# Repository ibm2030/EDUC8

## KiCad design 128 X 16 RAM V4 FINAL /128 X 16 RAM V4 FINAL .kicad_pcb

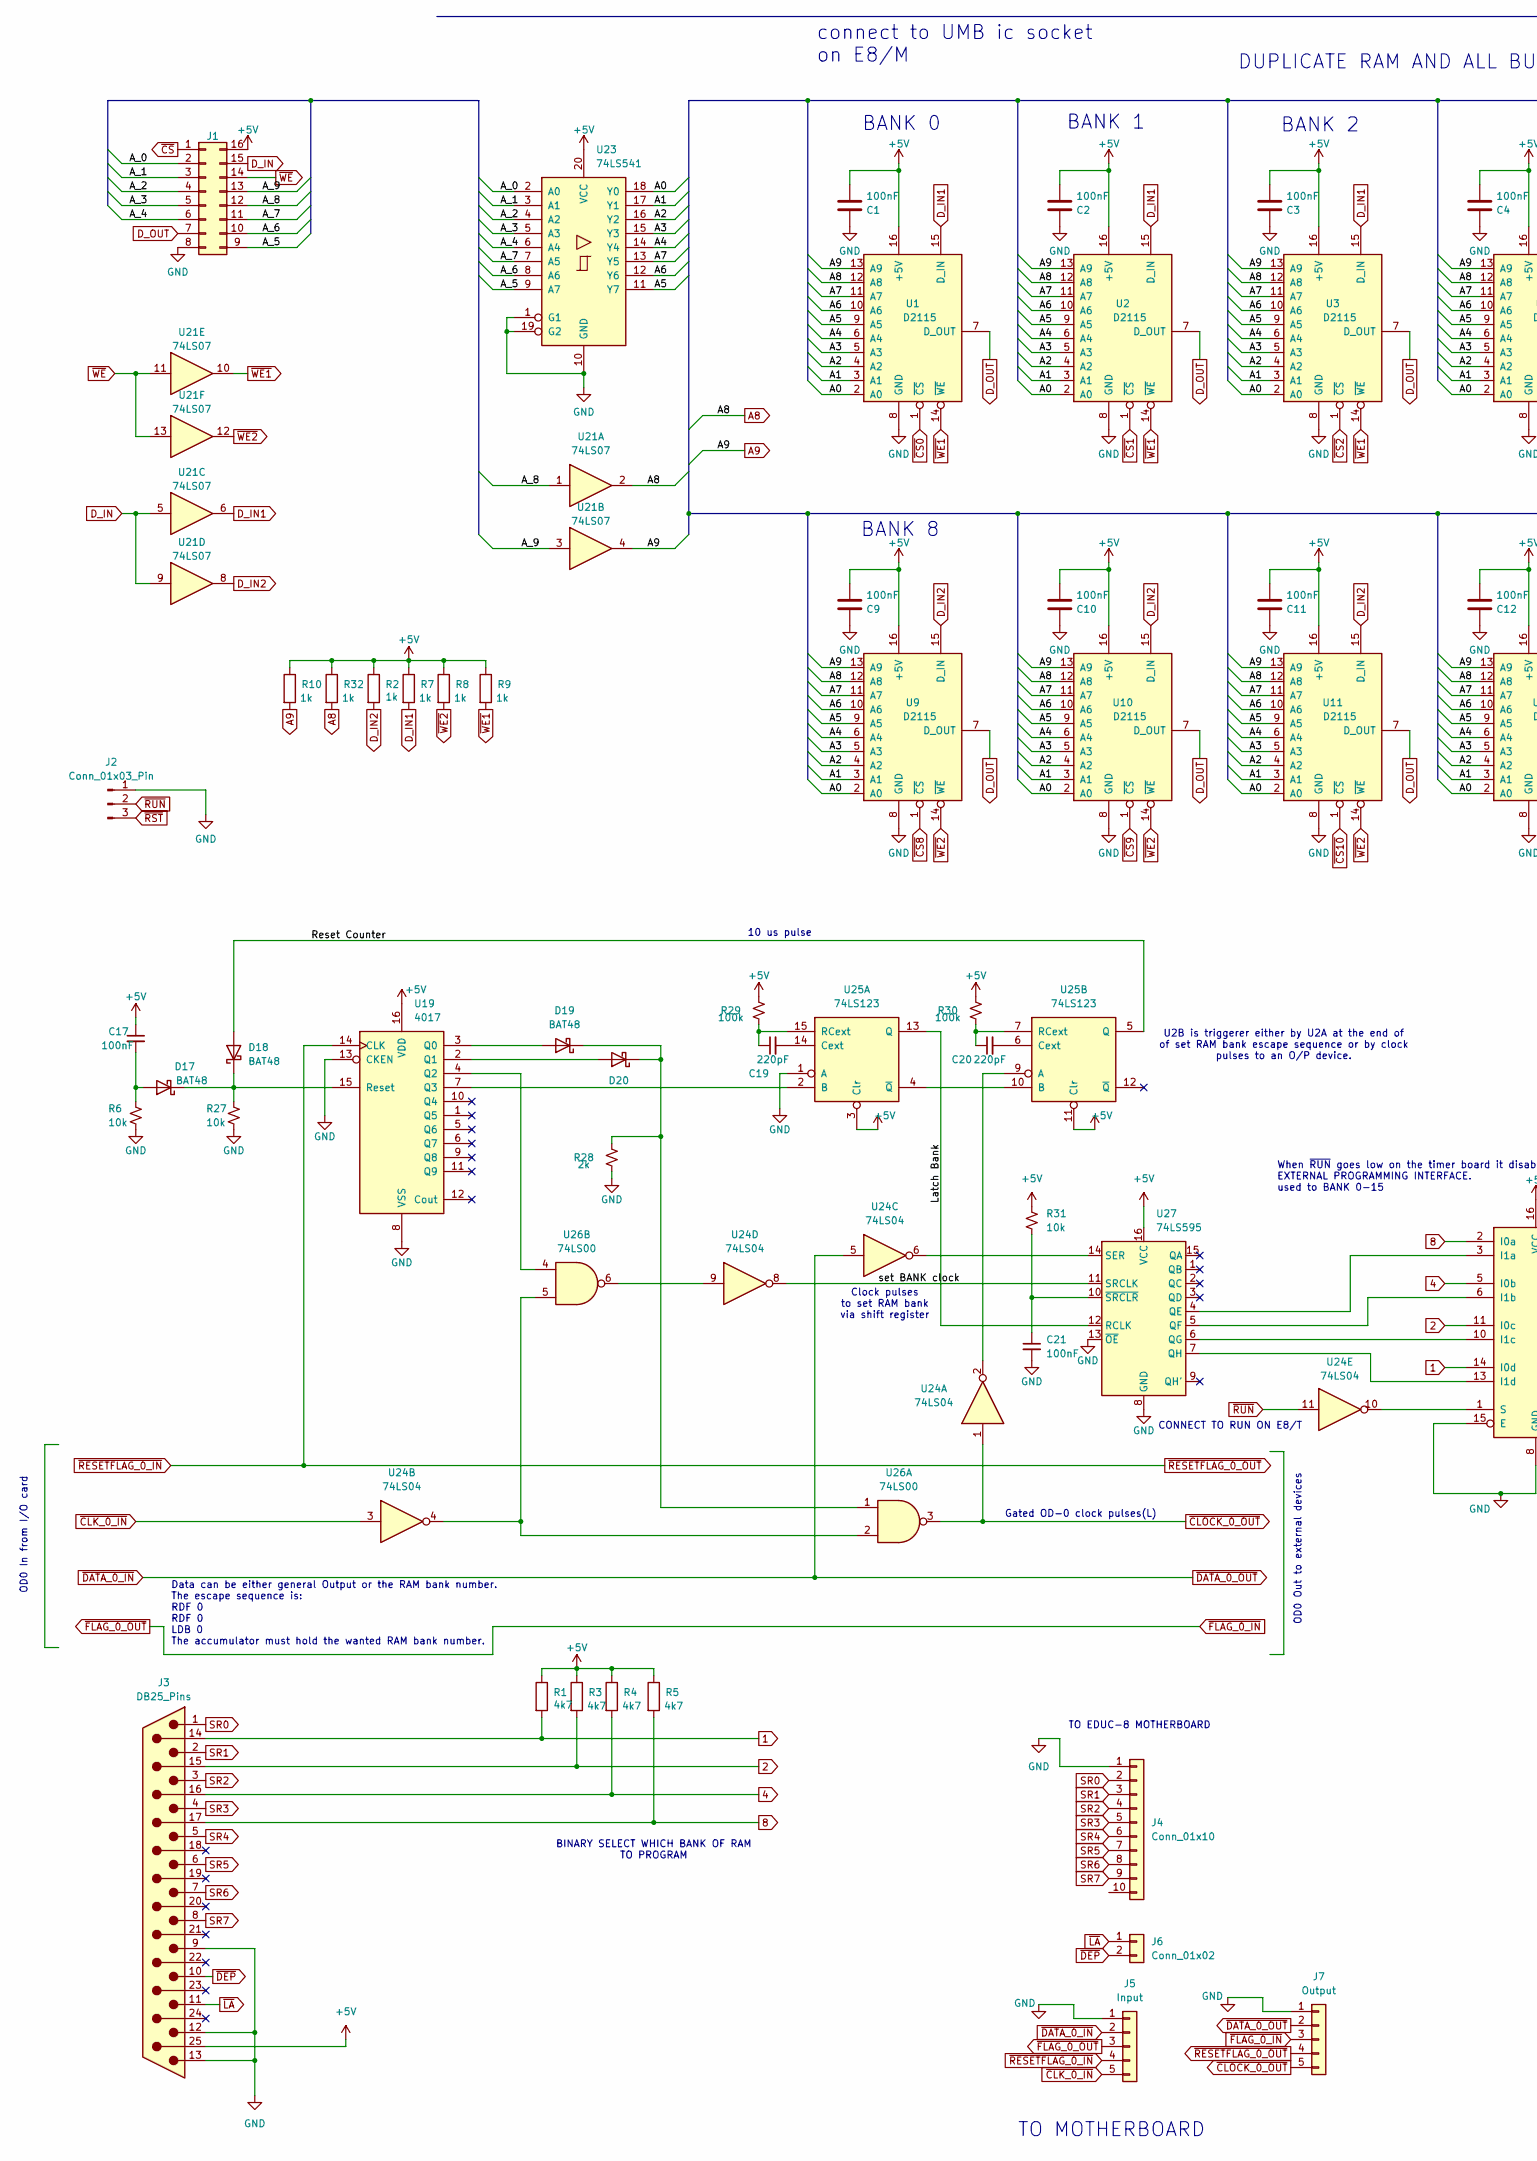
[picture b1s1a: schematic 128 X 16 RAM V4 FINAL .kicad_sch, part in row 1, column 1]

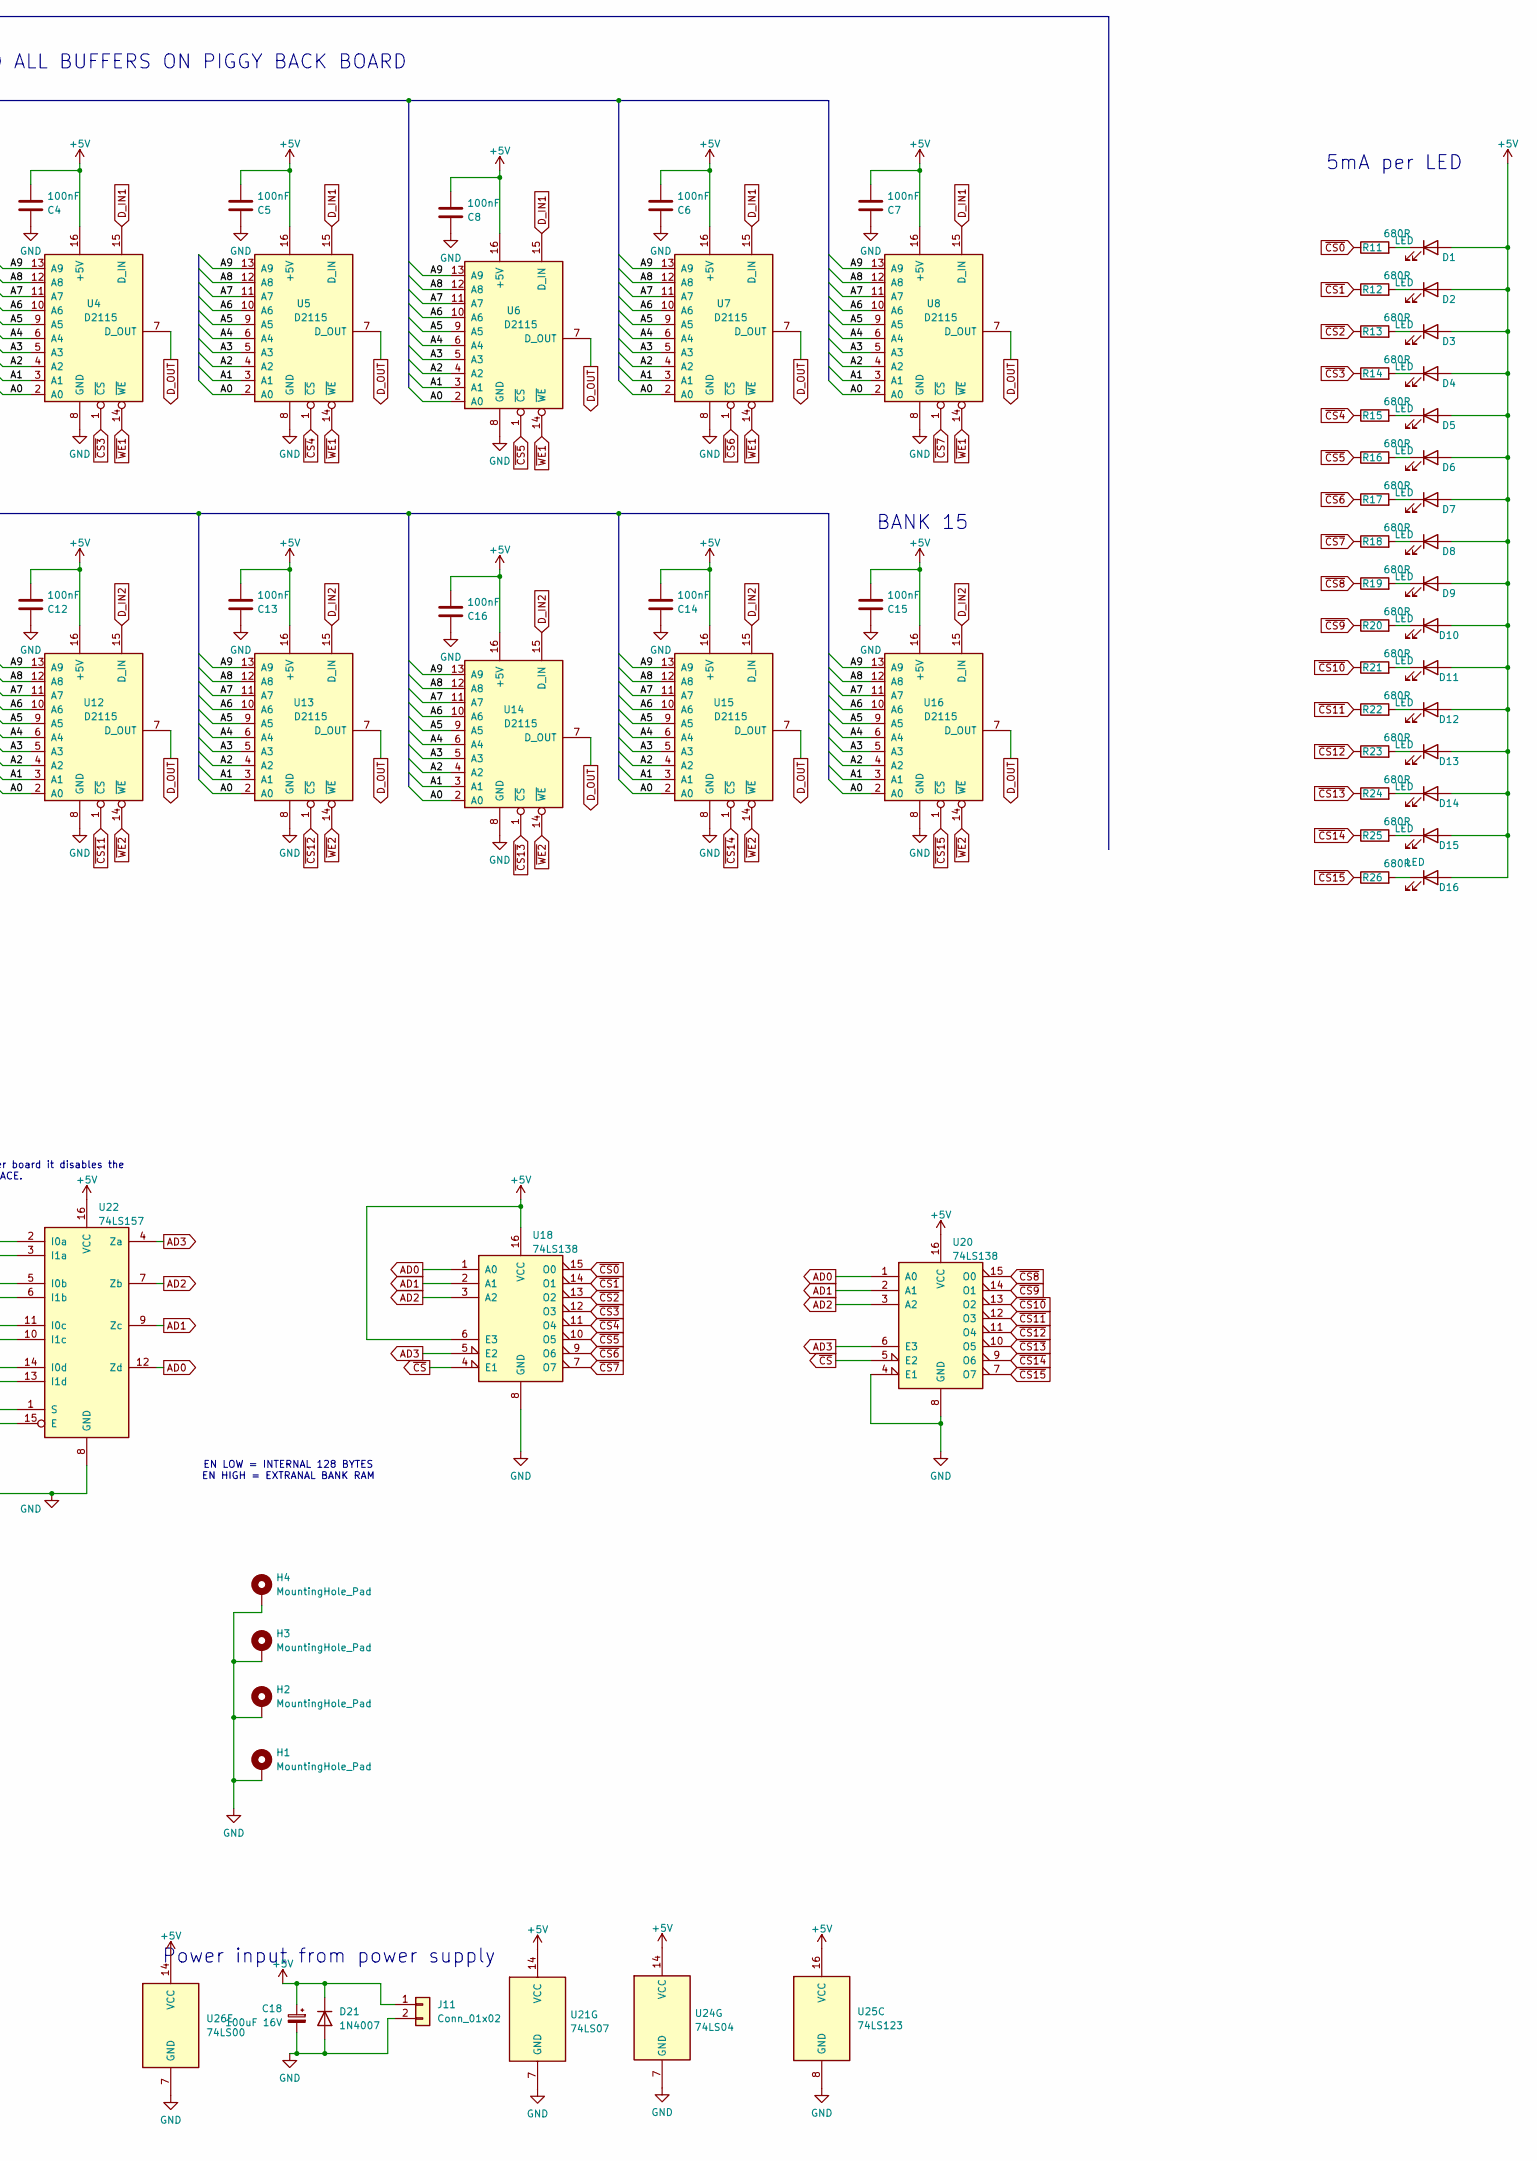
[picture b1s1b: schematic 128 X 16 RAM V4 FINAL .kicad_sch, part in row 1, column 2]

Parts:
C1, C2, C3, C4, C5, C6, C7, C8, C9, C10, C11, C12, C13, C14, C15, C16, C17, C21: 100nF; C_Disc_D4.3mm_W1.9mm_P5.00mm
C18: 100uF 16V; CP_Radial_D12.5mm_P5.00mm
C19, C20: 220pF; C_Disc_D4.3mm_W1.9mm_P5.00mm
D1, D2, D3, D4, D5, D6, D7, D8, D9, D10, D11, D12, D13, D14, D15, D16: LED; LED_D3.0mm
D17, D18, D19, D20: BAT48; D_DO-35_SOD27_P7.62mm_Horizontal
D21: 1N4007; D_DO-41_SOD81_P10.16mm_Horizontal
H1, H2, H3, H4: MountingHole_Pad; MountingHole_3.2mm_M3_DIN965_Pad
J1: Conn_02x08_Counter_Clockwise; DIP-16_W7.62mm_Socket_LongPads
J2: Conn_01x03_Pin; JST_XH_B3B-XH-A_1x03_P2.50mm_Vertical
J3: DB25_Pins; DSUB-25_Pins_Horizontal_P2.77x2.84mm_EdgePinOffset7.70mm_Ho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
J4: Conn_01x10; JST_XH_B10B-XH-A_1x10_P2.50mm_Vertical
J5: Input; JST_XH_B5B-XH-A_1x05_P2.50mm_Vertical
J6: Conn_01x02; JST_XH_B2B-XH-A_1x02_P2.50mm_Vertical
J7: Output; JST_XH_B5B-XH-A_1x05_P2.50mm_Vertical
J11: Conn_01x02; TerminalBlock_Phoenix_MKDS-1,5-2-5.08_1x02_P5.08mm_Horizont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
R1, R3, R4, R5: 4k7; R_Axial_DIN0207_L6.3mm_D2.5mm_P10.16mm_Horizontal
R2, R7, R8, R9, R10, R32: 1k; R_Axial_DIN0207_L6.3mm_D2.5mm_P10.16mm_Horizontal
R6, R27, R31: 10k; R_Axial_DIN0207_L6.3mm_D2.5mm_P10.16mm_Horizontal
R11, R12, R13, R14, R15, R16, R17, R18, R19, R20, R21, R22, R23, R24, R25, R26: 680R; R_Axial_DIN0207_L6.3mm_D2.5mm_P10.16mm_Horizontal
R28: 2k; R_Axial_DIN0207_L6.3mm_D2.5mm_P10.16mm_Horizontal
R29, R30: 100k; R_Axial_DIN0207_L6.3mm_D2.5mm_P10.16mm_Horizontal
U1, U2, U3, U4, U5, U6, U7, U8, U9, U10, U11, U12, U13, U14, U15, U16: D2115; DIP-16_W7.62mm_LongPads
U18, U20: 74LS138; DIP-16_W7.62mm_LongPads
U19: 4017; DIP-16_W7.62mm_LongPads
U21: 74LS07; DIP-14_W7.62mm_LongPads
U22: 74LS157; DIP-16_W7.62mm_LongPads
U23: 74LS541; DIP-20_W7.62mm_LongPads
U24: 74LS04; DIP-14_W7.62mm_LongPads
U25: 74LS123; DIP-16_W7.62mm_LongPads
U26: 74LS00; DIP-14_W7.62mm_LongPads
U27: 74LS595

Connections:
1: J3.14, R1.2, U22.14 (I0d)
2: J3.15, R3.2, U22.11 (I0c)
4: J3.16, R4.2, U22.5 (I0b)
8: J3.17, R5.2, U22.2 (I0a)
+5V: C1.2, C2.2, C3.2, C4.2, C5.2, C6.2, C7.2, C8.2, C9.2, C10.2, C11.2, C12.2, C13.2, C14.2, C15.2, C16.2, C17.1, C18.1, D1.2 (A), D2.2 (A), D3.2 (A), D4.2 (A), D5.2 (A), D6.2 (A), D7.2 (A), D8.2 (A), D9.2 (A), D10.2 (A), D11.2 (A), D12.2 (A), D13.2 (A), D14.2 (A), D15.2 (A), D16.2 (A), D21.1 (K), J1.16, J3.25, J11.1, R1.1, R2.1, R3.1, R4.1, R5.1, R7.1, R8.1, R9.1, R10.1, R29.1, R30.1, R31.1, R32.1, U1.16 (+5V), U2.16 (+5V), U3.16 (+5V), U4.16 (+5V), U5.16 (+5V), U6.16 (+5V), U7.16 (+5V), U8.16 (+5V), U9.16 (+5V), U10.16 (+5V), U11.16 (+5V), U12.16 (+5V), U13.16 (+5V), U14.16 (+5V), U15.16 (+5V), U16.16 (+5V), U18.6 (E3), U18.16 (VCC), U19.16 (VDD), U20.16 (VCC), U21.14 (VCC), U22.16 (VCC), U23.20 (VCC), U24.14 (VCC), U25.3 (Clr), U25.11 (Clr), U25.16 (VCC), U26.14 (VCC), U27.16 (VCC)
/A0: U1.2 (A0), U2.2 (A0), U3.2 (A0), U4.2 (A0), U5.2 (A0), U6.2 (A0), U7.2 (A0), U8.2 (A0), U9.2 (A0), U10.2 (A0), U11.2 (A0), U12.2 (A0), U13.2 (A0), U14.2 (A0), U15.2 (A0), U16.2 (A0), U23.18 (Y0)
/A1: U1.3 (A1), U2.3 (A1), U3.3 (A1), U4.3 (A1), U5.3 (A1), U6.3 (A1), U7.3 (A1), U8.3 (A1), U9.3 (A1), U10.3 (A1), U11.3 (A1), U12.3 (A1), U13.3 (A1), U14.3 (A1), U15.3 (A1), U16.3 (A1), U23.17 (Y1)
/A2: U1.4 (A2), U2.4 (A2), U3.4 (A2), U4.4 (A2), U5.4 (A2), U6.4 (A2), U7.4 (A2), U8.4 (A2), U9.4 (A2), U10.4 (A2), U11.4 (A2), U12.4 (A2), U13.4 (A2), U14.4 (A2), U15.4 (A2), U16.4 (A2), U23.16 (Y2)
/A3: U1.5 (A3), U2.5 (A3), U3.5 (A3), U4.5 (A3), U5.5 (A3), U6.5 (A3), U7.5 (A3), U8.5 (A3), U9.5 (A3), U10.5 (A3), U11.5 (A3), U12.5 (A3), U13.5 (A3), U14.5 (A3), U15.5 (A3), U16.5 (A3), U23.15 (Y3)
/A4: U1.6 (A4), U2.6 (A4), U3.6 (A4), U4.6 (A4), U5.6 (A4), U6.6 (A4), U7.6 (A4), U8.6 (A4), U9.6 (A4), U10.6 (A4), U11.6 (A4), U12.6 (A4), U13.6 (A4), U14.6 (A4), U15.6 (A4), U16.6 (A4), U23.14 (Y4)
/A5: U1.9 (A5), U2.9 (A5), U3.9 (A5), U4.9 (A5), U5.9 (A5), U6.9 (A5), U7.9 (A5), U8.9 (A5), U9.9 (A5), U10.9 (A5), U11.9 (A5), U12.9 (A5), U13.9 (A5), U14.9 (A5), U15.9 (A5), U16.9 (A5), U23.11 (Y7)
/A6: U1.10 (A6), U2.10 (A6), U3.10 (A6), U4.10 (A6), U5.10 (A6), U6.10 (A6), U7.10 (A6), U8.10 (A6), U9.10 (A6), U10.10 (A6), U11.10 (A6), U12.10 (A6), U13.10 (A6), U14.10 (A6), U15.10 (A6), U16.10 (A6), U23.12 (Y6)
/A7: U1.11 (A7), U2.11 (A7), U3.11 (A7), U4.11 (A7), U5.11 (A7), U6.11 (A7), U7.11 (A7), U8.11 (A7), U9.11 (A7), U10.11 (A7), U11.11 (A7), U12.11 (A7), U13.11 (A7), U14.11 (A7), U15.11 (A7), U16.11 (A7), U23.13 (Y5)
/A_0: J1.2, U23.2 (A0)
/A_1: J1.3, U23.3 (A1)
/A_2: J1.4, U23.4 (A2)
/A_3: J1.5, U23.5 (A3)
/A_4: J1.6, U23.6 (A4)
/A_5: J1.9, U23.9 (A7)
/A_6: J1.10, U23.8 (A6)
/A_7: J1.11, U23.7 (A5)
/A_8: J1.12, U21.1
/A_9: J1.13, U21.3
/Latch Bank: U25.13 (Q), U27.12 (RCLK)
/Reset Counter: D18.2 (A), U25.5 (Q)
/set BANK clock: U24.8, U27.11 (SRCLK)
A8: R32.2, U1.12 (A8), U2.12 (A8), U3.12 (A8), U4.12 (A8), U5.12 (A8), U6.12 (A8), U7.12 (A8), U8.12 (A8), U9.12 (A8), U10.12 (A8), U11.12 (A8), U12.12 (A8), U13.12 (A8), U14.12 (A8), U15.12 (A8), U16.12 (A8), U21.2
A9: R10.2, U1.13 (A9), U2.13 (A9), U3.13 (A9), U4.13 (A9), U5.13 (A9), U6.13 (A9), U7.13 (A9), U8.13 (A9), U9.13 (A9), U10.13 (A9), U11.13 (A9), U12.13 (A9), U13.13 (A9), U14.13 (A9), U15.13 (A9), U16.13 (A9), U21.4
AD0: U18.1 (A0), U20.1 (A0), U22.12 (Zd)
AD1: U18.2 (A1), U20.2 (A1), U22.9 (Zc)
AD2: U18.3 (A2), U20.3 (A2), U22.7 (Zb)
AD3: U18.5 (E2), U20.6 (E3), U22.4 (Za)
D_IN: J1.15, U21.5, U21.9
D_IN1: R7.2, U1.15 (D_IN), U2.15 (D_IN), U3.15 (D_IN), U4.15 (D_IN), U5.15 (D_IN), U6.15 (D_IN), U7.15 (D_IN), U8.15 (D_IN), U21.6
D_IN2: R2.2, U9.15 (D_IN), U10.15 (D_IN), U11.15 (D_IN), U12.15 (D_IN), U13.15 (D_IN), U14.15 (D_IN), U15.15 (D_IN), U16.15 (D_IN), U21.8
D_OUT: J1.7, U1.7 (D_OUT), U2.7 (D_OUT), U3.7 (D_OUT), U4.7 (D_OUT), U5.7 (D_OUT), U6.7 (D_OUT), U7.7 (D_OUT), U8.7 (D_OUT), U9.7 (D_OUT), U10.7 (D_OUT), U11.7 (D_OUT), U12.7 (D_OUT), U13.7 (D_OUT), U14.7 (D_OUT), U15.7 (D_OUT), U16.7 (D_OUT)
GND: C1.1, C2.1, C3.1, C4.1, C5.1, C6.1, C7.1, C8.1, C9.1, C10.1, C11.1, C12.1, C13.1, C14.1, C15.1, C16.1, C18.2, C21.2, D21.2 (A), H1.1, H2.1, H3.1, H4.1, J1.8, J2.1, J3.9, J3.12, J3.13, J4.1, J5.1, J7.1, J11.2, R6.2, R27.2, R28.2, U1.8 (GND), U2.8 (GND), U3.8 (GND), U4.8 (GND), U5.8 (GND), U6.8 (GND), U7.8 (GND), U8.8 (GND), U9.8 (GND), U10.8 (GND), U11.8 (GND), U12.8 (GND), U13.8 (GND), U14.8 (GND), U15.8 (GND), U16.8 (GND), U18.8 (GND), U19.8 (VSS), U19.13 (CKEN), U20.4 (E1), U20.8 (GND), U21.7 (GND), U22.8 (GND), U22.15 (E), U23.1 (G1), U23.10 (GND), U23.19 (G2), U24.7 (GND), U25.1 (A), U25.8 (GND), U26.7 (GND), U27.8 (GND), U27.13 (~OE)
unnamed: D1.1 (K), R11.2
unnamed: D2.1 (K), R12.2
unnamed: D3.1 (K), R13.2
unnamed: D4.1 (K), R14.2
unnamed: D5.1 (K), R15.2
unnamed: D6.1 (K), R16.2
unnamed: D7.1 (K), R17.2
unnamed: D8.1 (K), R18.2
unnamed: D9.1 (K), R19.2
unnamed: D10.1 (K), R20.2
unnamed: D11.1 (K), R21.2
unnamed: D12.1 (K), R22.2
unnamed: D13.1 (K), R23.2
unnamed: D14.1 (K), R24.2
unnamed: D15.1 (K), R25.2
unnamed: D16.1 (K), R26.2
unnamed: C17.2, D17.2 (A), R6.1
unnamed: D17.1 (K), D18.1 (K), R27.1, U19.15 (Reset)
unnamed: D19.2 (A), U19.3 (Q0)
unnamed: D19.1 (K), D20.1 (K), R28.1, U26.1
unnamed: D20.2 (A), U19.2 (Q1)
unnamed: U19.4 (Q2), U26.4
unnamed: U19.7 (Q3), U25.2 (B)
unnamed: U22.3 (I1a), U27.4 (QE)
unnamed: U22.6 (I1b), U27.5 (QF)
unnamed: U22.10 (I1c), U27.6 (QG)
unnamed: U22.13 (I1d), U27.7 (QH)
unnamed: U22.1 (S), U24.10
unnamed: U24.4, U26.2, U26.5
unnamed: U24.9, U26.6
unnamed: C19.2, U25.14 (Cext)
unnamed: C19.1, R29.2, U25.15 (RCext)
unnamed: U25.4 (~Q), U25.10 (B)
unnamed: U24.2, U25.9 (A)
unnamed: C20.2, U25.6 (Cext)
unnamed: C20.1, R30.2, U25.7 (RCext)
unnamed: U24.6, U27.14 (SER)
unnamed: C21.1, R31.2, U27.10 (~SRCLR)
SR0: J3.1, J4.2
SR1: J3.2, J4.3
SR2: J3.3, J4.4
SR3: J3.4, J4.5
SR4: J3.5, J4.6
SR5: J3.6, J4.7
SR6: J3.7, J4.8
SR7: J3.8, J4.9
~CLK_0_IN: J5.5, U24.3
~CLOCK_0_OUT: J7.5, U24.1, U26.3
~CS0: R11.1, U1.1 (~CS), U18.15 (O0)
~CS1: R12.1, U2.1 (~CS), U18.14 (O1)
~CS2: R13.1, U3.1 (~CS), U18.13 (O2)
~CS3: R14.1, U4.1 (~CS), U18.12 (O3)
~CS4: R15.1, U5.1 (~CS), U18.11 (O4)
~CS5: R16.1, U6.1 (~CS), U18.10 (O5)
~CS6: R17.1, U7.1 (~CS), U18.9 (O6)
~CS7: R18.1, U8.1 (~CS), U18.7 (O7)
~CS8: R19.1, U9.1 (~CS), U20.15 (O0)
~CS9: R20.1, U10.1 (~CS), U20.14 (O1)
~CS10: R21.1, U11.1 (~CS), U20.13 (O2)
~CS11: R22.1, U12.1 (~CS), U20.12 (O3)
~CS12: R23.1, U13.1 (~CS), U20.11 (O4)
~CS13: R24.1, U14.1 (~CS), U20.10 (O5)
~CS14: R25.1, U15.1 (~CS), U20.9 (O6)
~CS15: R26.1, U16.1 (~CS), U20.7 (O7)
~CS: J1.1, U18.4 (E1), U20.5 (E2)
~DATA_0_IN: J5.2, J7.2, U24.5
~DEP: J3.10, J6.2
~FLAG_0_IN: J5.3, J7.3
~LA: J3.11, J6.1
~RESETFLAG_0_IN: J5.4, J7.4, U19.14 (CLK)
~RST: J2.3
~RUN: J2.2, U24.11
~WE1: R9.2, U1.14 (~WE), U2.14 (~WE), U3.14 (~WE), U4.14 (~WE), U5.14 (~WE), U6.14 (~WE), U7.14 (~WE), U8.14 (~WE), U21.10
~WE2: R8.2, U9.14 (~WE), U10.14 (~WE), U11.14 (~WE), U12.14 (~WE), U13.14 (~WE), U14.14 (~WE), U15.14 (~WE), U16.14 (~WE), U21.12
~WE: J1.14, U21.11, U21.13

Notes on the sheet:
connect to UMB ic socket on E8/M
10 us pulse
BANK 15
EN LOW = INTERNAL 128 BYTES EN HIGH = EXTRANAL BANK RAM
BANK 0
DUPLICATE RAM AND ALL BUFFERS ON PIGGY BACK BOARD
Gated OD-0 clock pulses(L)
TO EDUC-8 MOTHERBOARD
OD0 Out to external devices
When ~{RUN} goes low on the timer board it disables the EXTERNAL PROGRAMMING INTERFACE. used to BANK 0-15
OD0 In from I/O card
Clock pulses to set RAM bank via shift register
Power input from power supply
BANK 8
5mA per LED
Data can be either general Output or the RAM bank number. The escape sequence is: RDF 0 RDF 0 LDB 0 The accumulator must hold the wanted RAM bank number.
BANK 1
BANK 2
CONNECT TO RUN ON E8/T
TO MOTHERBOARD
U2B is triggerer either by U2A at the end of of set RAM bank escape sequence or by clock pulses to an O/P device.
BINARY SELECT WHICH BANK OF RAM TO PROGRAM

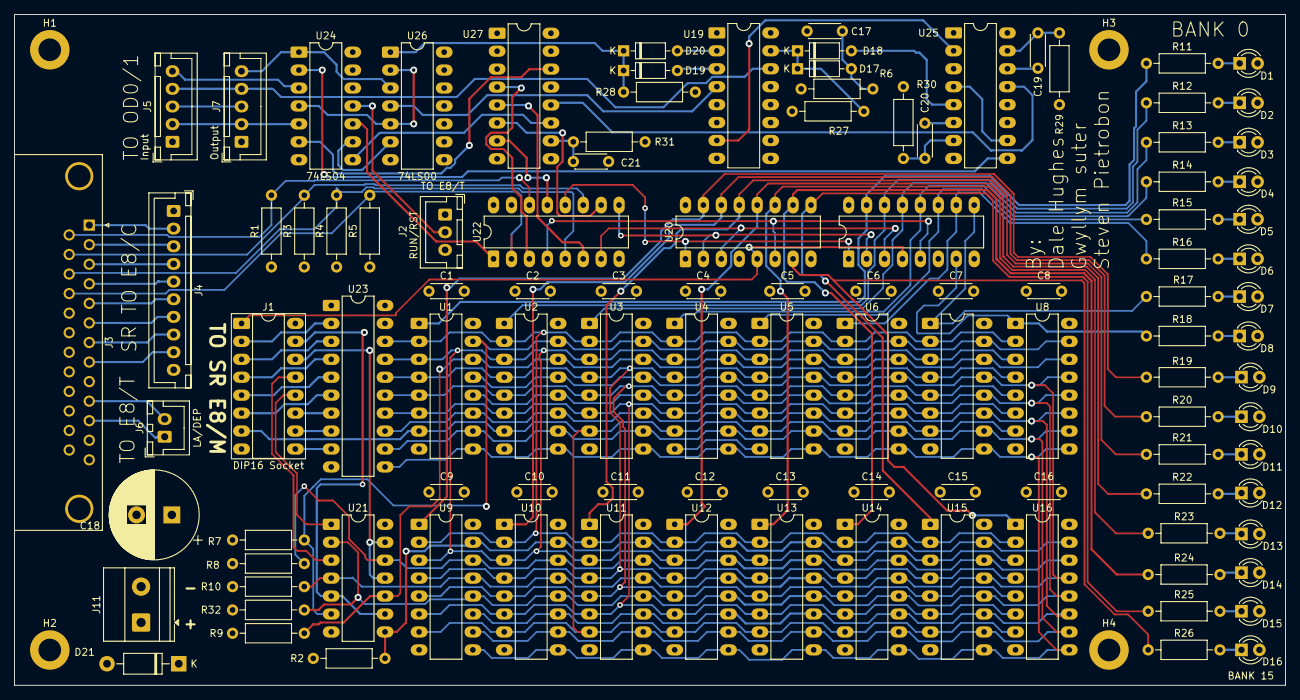
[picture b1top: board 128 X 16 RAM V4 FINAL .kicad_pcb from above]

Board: 4 copper layers, 180.0 x 95.0 mm, 112 parts (0 on the bottom side), 111 nets.

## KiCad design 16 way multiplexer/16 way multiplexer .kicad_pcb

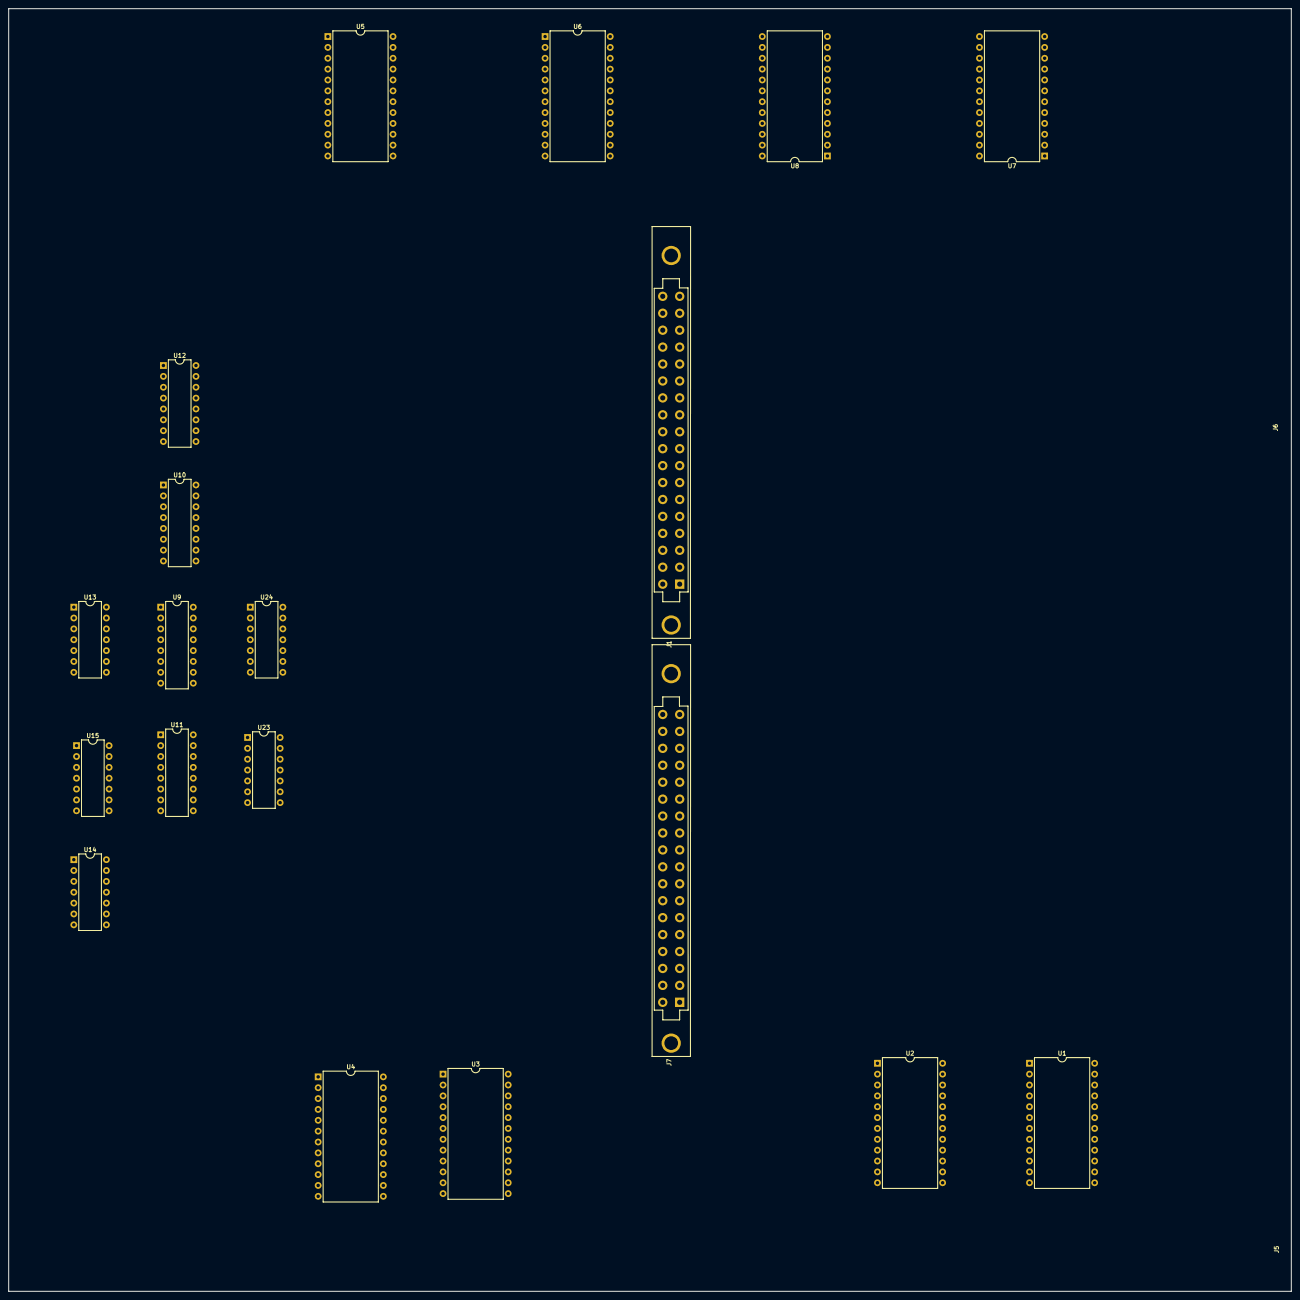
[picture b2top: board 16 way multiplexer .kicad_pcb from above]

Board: 4 copper layers, 300.0 x 300.0 mm, 21 parts (0 on the bottom side), 34 nets, no tracks yet.

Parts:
J1, J7: 36-way-edge-connector-Educ-8-connectors; 36_way_3.96mm_card_edge_socket
J5: 36-way-pcb-edge-Educ-8-connectors; PCB_36pin
J6: 18-way-pcb-edge-Educ-8-connectors; PCB_18pin
U1, U2, U3, U5, U6: 74LS154; DIP-24_W15.24mm
U4, U7, U8: 74LS150; DIP-24_W15.24mm
U9, U10, U11, U12: 74LS75; DIP-16_W7.62mm
U13: 74LS164; DIP-14_W7.62mm
U14, U15: 7400; DIP-14_W7.62mm
U23, U24: 74LS07; DIP-14_W7.62mm

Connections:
GND: J1.H1, J1.H2
LAM0: U9.16, U24.5
LAM2: U9.10, U24.9, U24.11
LAM3: U9.9, U24.13
LAR0: U5.23, U6.23, U7.15, U8.15, U12.16, U23.11
LAR1: U5.22, U6.22, U7.14, U8.14, U12.15
LAR2: U5.21, U6.21, U7.13, U8.13, U12.10, U24.1
LAR3: U5.20, U6.20, U7.11, U8.11, U12.9, U24.3
LAS0: U1.23, U2.23, U3.23, U4.15, U11.16, U23.1
LAS1: U1.22, U2.22, U3.22, U4.14, U11.15, U23.3
LAS2: U1.21, U2.21, U3.21, U4.13, U11.10, U23.5
LAS3: U1.20, U2.20, U3.20, U4.11, U11.9, U23.9
unnamed: U11.4, U11.13, U14.3
unnamed: U14.1, U14.2, U14.6
OD_0_RST: J1.13, J1.N
SA0: J1.5, J1.E, U9.2, U10.2, U11.2, U12.2, U13.13
SA1: J1.6, J1.F, U9.3, U10.3, U11.3, U12.3, U13.12
SA2: J1.7, J1.G, U9.6, U10.6, U11.6, U12.6, U13.11
SA3: J1.8, J1.H, U9.7, U10.7, U11.7, U12.7, U13.10
SA4: J1.9, J1.J, U13.6
SA5: J1.10, J1.K, U13.5
SA6: J1.11, J1.L, U13.4
SA7: J1.12, J1.M, U13.3
~CLK_R0: J1.16, J1.17, J1.R, J1.S, U5.1, U6.1
~CLK_R1: U5.2, U6.2
~CLK_R2: U5.3, U6.3
~CLK_R3: U5.4, U6.4
~CLK_S0: J1.1, J1.A, U1.1
~DATA_R0: J1.14, J1.P, U7.8
~DATA_S0: J1.4, J1.D, U3.1
~FLAG_R0: J1.15, J1.Q, U8.8
~FLAG_S0: J1.3, J1.C, U4.8
~FLAG_S7: U4.1, U8.1
~RST_S0: J1.2, J1.B, U2.1

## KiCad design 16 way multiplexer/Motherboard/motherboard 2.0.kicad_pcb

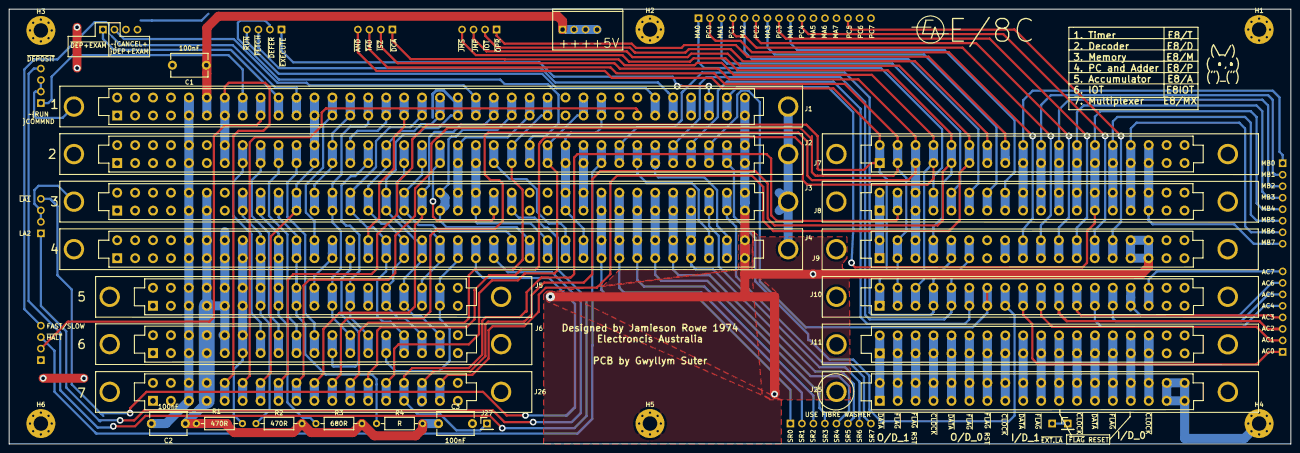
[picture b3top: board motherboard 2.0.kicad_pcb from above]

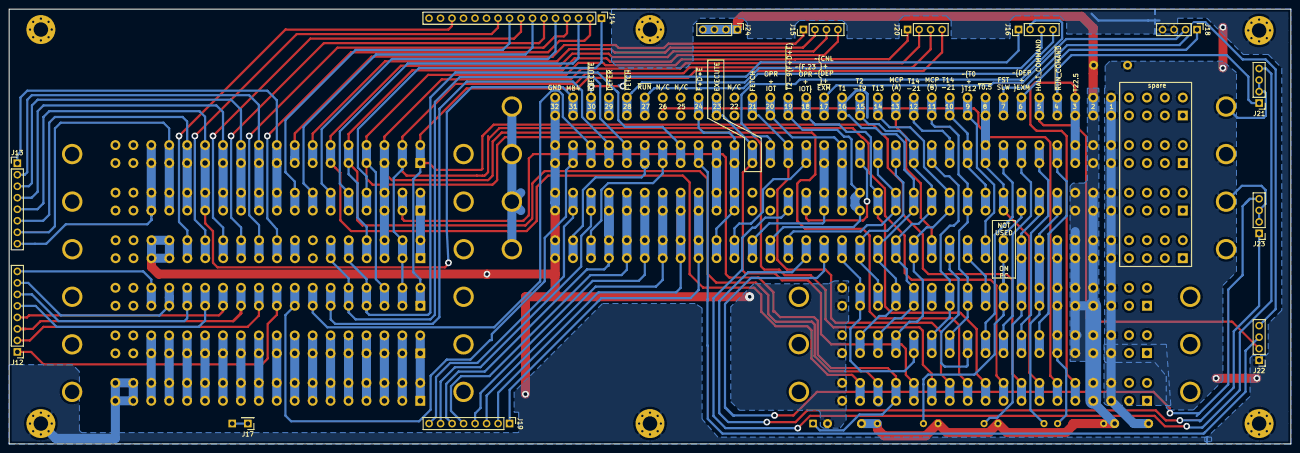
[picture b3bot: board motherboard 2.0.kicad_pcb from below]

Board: 2 copper layers, 283.0 x 96.0 mm, 41 parts (13 on the bottom side), 120 nets.

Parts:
C1, C2, C3: 100nF; C_Disc_D8.0mm_W5.0mm_P7.50mm
H1, H2, H3, H4, H5, H6: MountingHole_Pad; MountingHole_3.2mm_M3_Pad_Via
J1: E8/T; 72_way_3.96mm_card_edge_socket
J2, J3, J4: 36-way-pcb-edge-socket-Educ-8-connectors; 72_way_3.96mm_card_edge_socket
J5, J6, J7, J8, J9, J10, J11, J25, J26: 36-way-edge-connector; 36_way_3.96mm_card_edge_socket
J12, J13, J19: Conn_01x08_Female; PinHeader_1x08_P2.54mm_Vertical
J14: Conn_01x16_Female; PinHeader_1x16_P2.54mm_Vertical
J15, J16, J18, J20, J21, J22, J23, J24: Conn_01x04_Female; PinHeader_1x04_P2.54mm_Vertical
J17, J27, J29: Conn_01x01_Female; PinHeader_1x01_P2.54mm_Vertical
R1, R2: 470R; R_Axial_DIN0207_L6.3mm_D2.5mm_P10.16mm_Horizontal
R3: 680R; R_Axial_DIN0207_L6.3mm_D2.5mm_P10.16mm_Horizontal
R4: R; R_Axial_DIN0207_L6.3mm_D2.5mm_P10.16mm_Horizontal

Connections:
+5V: C1.1, C2.1, C3.1, J1.6, J1.A6, J2.6, J2.A6, J3.6, J3.7, J3.A6, J3.A7, J4.6, J4.7, J4.A6, J4.A7, J5.4, J5.5, J5.D, J5.E, J6.4, J6.5, J6.D, J6.E, J24.1, J24.2, J24.3, J24.4, J26.4, J26.D, R1.2, R2.2, R3.2, R4.2
A-BUS: J4.8, J4.A8, J5.6, J5.F, J6.6, J6.F, R1.1
AC0: J10.9, J10.J, J12.1
AC0_TO_IOT: J5.13, J5.N
AC1: J10.10, J10.K, J12.2
AC2: J10.11, J10.L, J12.3
AC3: J10.12, J10.M, J12.4
AC4: J10.13, J10.N, J12.5
AC5: J10.14, J10.P, J12.6
AC6: J10.15, J10.Q, J12.7
AC7: J10.16, J10.R, J12.8
AC=0: J4.20, J4.A20, J5.17, J5.S, J6.14, J6.P
AC=-VE: J9.8, J9.H
B-BUS: J3.8, J3.A8, J4.9, J4.A9, J5.7, J5.G, R2.1
C-BUS: J3.9, J3.A9, J4.10, J4.A10, J5.8, J5.H, R3.1
D-BUS: J3.10, J3.A10, J4.11, J4.A11, J5.9, J5.J, R4.1
EXECUTE: J1.27, J1.A27, J2.25, J2.A25, J26.14, J26.P
F.2-9(F+D+E): J1.23, J1.A23, J3.19, J3.A19, J4.24, J4.A24
FAST_SLOW: J1.11, J1.A11, J22.4
FETCH: J1.25, J1.A25, J2.23, J2.A23, J26.12, J26.M
GND: C1.2, C2.2, C3.2, H1.1, H2.1, H3.1, H4.1, H5.1, H6.1, J1.5, J1.36, J1.A5, J1.A36, J1.H1, J1.H2, J2.5, J2.36, J2.A5, J2.A36, J2.H1, J2.H2, J3.5, J3.36, J3.A5, J3.A36, J3.H1, J3.H2, J4.5, J4.36, J4.A5, J4.A36, J4.H1, J4.H2, J5.3, J5.18, J5.C, J5.T, J6.3, J6.18, J6.C, J6.T, J9.15, J9.16, J9.Q, J9.R, J18.3, J18.4, J21.2, J21.3, J22.1, J23.2, J23.3, J25.17, J25.18, J25.S, J25.T, J26.3, J26.18, J26.C, J26.T
ID0~CLK: J11.16, J11.R, J25.16, J25.R
ID0~DATA: J11.13, J11.N, J25.13, J25.N
ID0~FLAG_RESET: J11.15, J11.Q, J25.15, J25.Q
ID0~FLAG: J11.14, J11.P, J25.14, J25.P
ID1~CLK: J11.12, J11.M, J25.12, J25.M
ID1~DATA: J11.9, J11.J, J25.9, J25.J
ID1~FLAG_RESET: J11.11, J11.L, J25.11, J25.L
ID1~FLAG: J11.10, J11.K, J25.10, J25.K
IO_DEVICE_SELECT: J2.8, J2.A8, J6.7, J6.G
IO_GATING: J2.9, J2.A9, J6.8, J6.H
JMS+DCA: J2.19, J2.A19, J3.22, J3.A22
LA2: J4.22, J4.A22, J23.1
MA0: J8.4, J8.D, J14.1
MA1: J8.5, J8.E, J14.3
MA2: J8.6, J8.F, J14.5
MA3: J8.7, J8.G, J14.7
MA4: J8.8, J8.H, J14.9
MB0: J7.9, J7.J, J8.9, J8.J, J13.1
MB1: J7.10, J7.K, J8.10, J8.K, J13.2
MB2: J7.11, J7.L, J8.11, J8.L, J13.3
MB3: J7.12, J7.M, J8.12, J8.M, J13.4
MB4: J1.35, J1.A35, J7.13, J7.N, J8.13, J8.N, J13.5
MB5: J7.14, J7.P, J8.14, J8.P, J13.6
MB6: J7.15, J7.Q, J8.15, J8.Q, J13.7
MB7: J7.16, J7.R, J8.16, J8.R, J13.8
MB=0: J8.1, J8.A, J9.1, J9.A
MCPA: J1.17, J1.A17, J4.15, J4.A15
MCPB: J1.15, J1.A15, J3.13, J3.A13, J5.11, J5.L, J6.12, J6.M
MEM.ENABLE: J2.27, J2.A27, J3.27, J3.A27
OD0~CLK: J11.8, J11.H, J25.8, J25.H
OD0~DATA: J11.5, J11.E, J25.5, J25.E
OD0~FLAG_RESET: J11.7, J11.G, J25.7, J25.G
OD0~FLAG: J11.6, J11.F, J25.6, J25.F
OD1_~DATA: J11.1, J11.A, J25.1, J25.A
OD1~CLK: J11.4, J11.D, J25.4, J25.D
OD1~FLAG_RESET: J11.3, J11.C, J25.3, J25.C
OD1~FLAG: J11.2, J11.B, J25.2, J25.B
OPR+IOT: J1.24, J1.A24, J2.20, J2.A20, J3.20, J3.A20
PC0: J9.9, J9.J, J14.2
PC1: J9.10, J9.K, J14.4
PC2: J9.11, J9.L, J14.6
PC3: J9.12, J9.M, J14.8
PC4: J9.13, J9.N, J14.10
PC5: J9.14, J9.P, J14.14
SKP_ON_IOT_FLAG: J2.11, J2.A11, J6.10, J6.K
SR0: J3.28, J3.A28, J4.28, J4.A28, J19.1
SR1: J3.29, J3.A29, J4.29, J4.A29, J19.2
SR2: J3.30, J3.A30, J4.30, J4.A30, J19.3
SR3: J3.31, J3.A31, J4.31, J4.A31, J19.4
SR4: J3.32, J3.A32, J4.32, J4.A32, J19.5
SR5: J3.33, J3.A33, J4.33, J4.A33, J19.6
SR6: J3.34, J3.A34, J19.7
SR7: J3.35, J3.A35, J19.8
T1: J1.20, J1.A20, J3.16, J3.A16, J4.18, J4.A18, J5.15, J5.Q, J6.17, J6.S
T2-9: J1.19, J1.A19, J2.16, J2.A16, J3.15, J3.A15, J4.17, J4.A17, J5.14, J5.P, J6.16, J6.R
T2-9.ISZ: J2.18, J2.A18, J3.17, J3.A17, J4.23, J4.A23
T13: J1.18, J1.A18, J3.14, J3.A14, J4.16, J4.A16, J6.15, J6.Q
T14-21: J1.14, J1.16, J1.A14, J1.A16, J2.13, J2.14, J2.A13, J2.A14, J3.12, J3.A12
T22.5: J1.7, J1.A7, J2.7, J2.A7, J26.5, J26.E
Z-BIT: J8.2, J26.15, J26.Q, J27.1
~AND: J7.1, J7.A, J10.1, J10.A, J20.4, J26.8, J26.H
~CANCEL+DEP+EXM: J1.21, J1.A21, J18.2
~CLA: J2.35, J2.A35, J10.8, J10.H
~CLEAR_IOT_FLAG: J2.10, J2.A10, J6.9, J6.J
~CMA: J2.34, J2.A34, J10.7, J10.G
~DCA: J7.4, J7.D, J10.3, J10.C, J20.1, J26.13, J26.N
~DEFER: J1.33, J1.A33, J2.24, J2.A24, J16.2
~DEP+EXM: J1.10, J1.A10, J18.1
~DEP: J3.23, J3.A23, J21.4
~EXEC: J1.34, J1.A34, J16.1
~EXT.LA: J17.1, J29.1
~F+D+E: J1.28, J1.A28, J2.26, J2.A26, J3.26, J3.A26, J4.27, J4.A27
~F.T23.OPR+IOT: J1.22, J1.A22, J3.18, J3.A18, J26.10, J26.K
~FETCH: J1.32, J1.A32, J16.3
~HLT_COMMAND: J1.9, J1.A9, J22.2
~HLT: J2.28, J2.A28, J22.3
~IAC: J2.32, J2.A32, J9.6, J9.F, J10.5, J10.E
~IOT_SHIFT: J2.15, J2.A15, J5.12, J5.M, J6.13, J6.N
~IOT_SKP: J4.14, J4.A14, J6.11, J6.L
~IOT: J7.7, J7.G, J15.2
~ISZ: J7.3, J7.C, J8.3, J8.C, J9.3, J9.C, J20.2, J26.11, J26.L
~JMP: J7.6, J7.F, J15.3, J26.17, J26.S
~JMS: J7.5, J7.E, J9.4, J9.D, J15.4, J26.16, J26.R
~LA1: J4.21, J4.A21, J23.4
~OPR: J7.8, J7.H, J15.1
~RAL: J2.33, J2.A33, J10.6, J10.F
~RAR: J2.29, J2.A29, J9.5, J9.E, J10.4, J10.D
~RST: J1.30, J1.A30, J26.6, J26.F
~RUN_COMMAND: J1.8, J1.A8, J21.1
~RUN: J1.31, J1.A31, J16.4
~SMA: J2.30, J2.A30, J4.34, J4.A34
~SZA: J2.31, J2.A31, J4.35, J4.A35
~T0+T12: J1.13, J1.A13, J4.12, J4.A12
~T0.5: J1.12, J1.A12, J2.12, J2.A12, J3.11, J3.A11, J26.7, J26.G
~T2-9.(TAD+IAC+CMA): J2.17, J2.A17, J4.19, J4.A19, J5.16, J5.R
~T13.RAR: J4.13, J4.A13, J5.10, J5.K
~T14-21(JMS+JMP): J2.21, J2.A21, J3.21, J3.A21, J4.25, J4.A25
~T14-21.SKP: J2.22, J2.A22, J4.26, J4.A26
~TAD: J7.2, J7.B, J9.2, J9.B, J10.2, J10.B, J20.3, J26.9, J26.J
